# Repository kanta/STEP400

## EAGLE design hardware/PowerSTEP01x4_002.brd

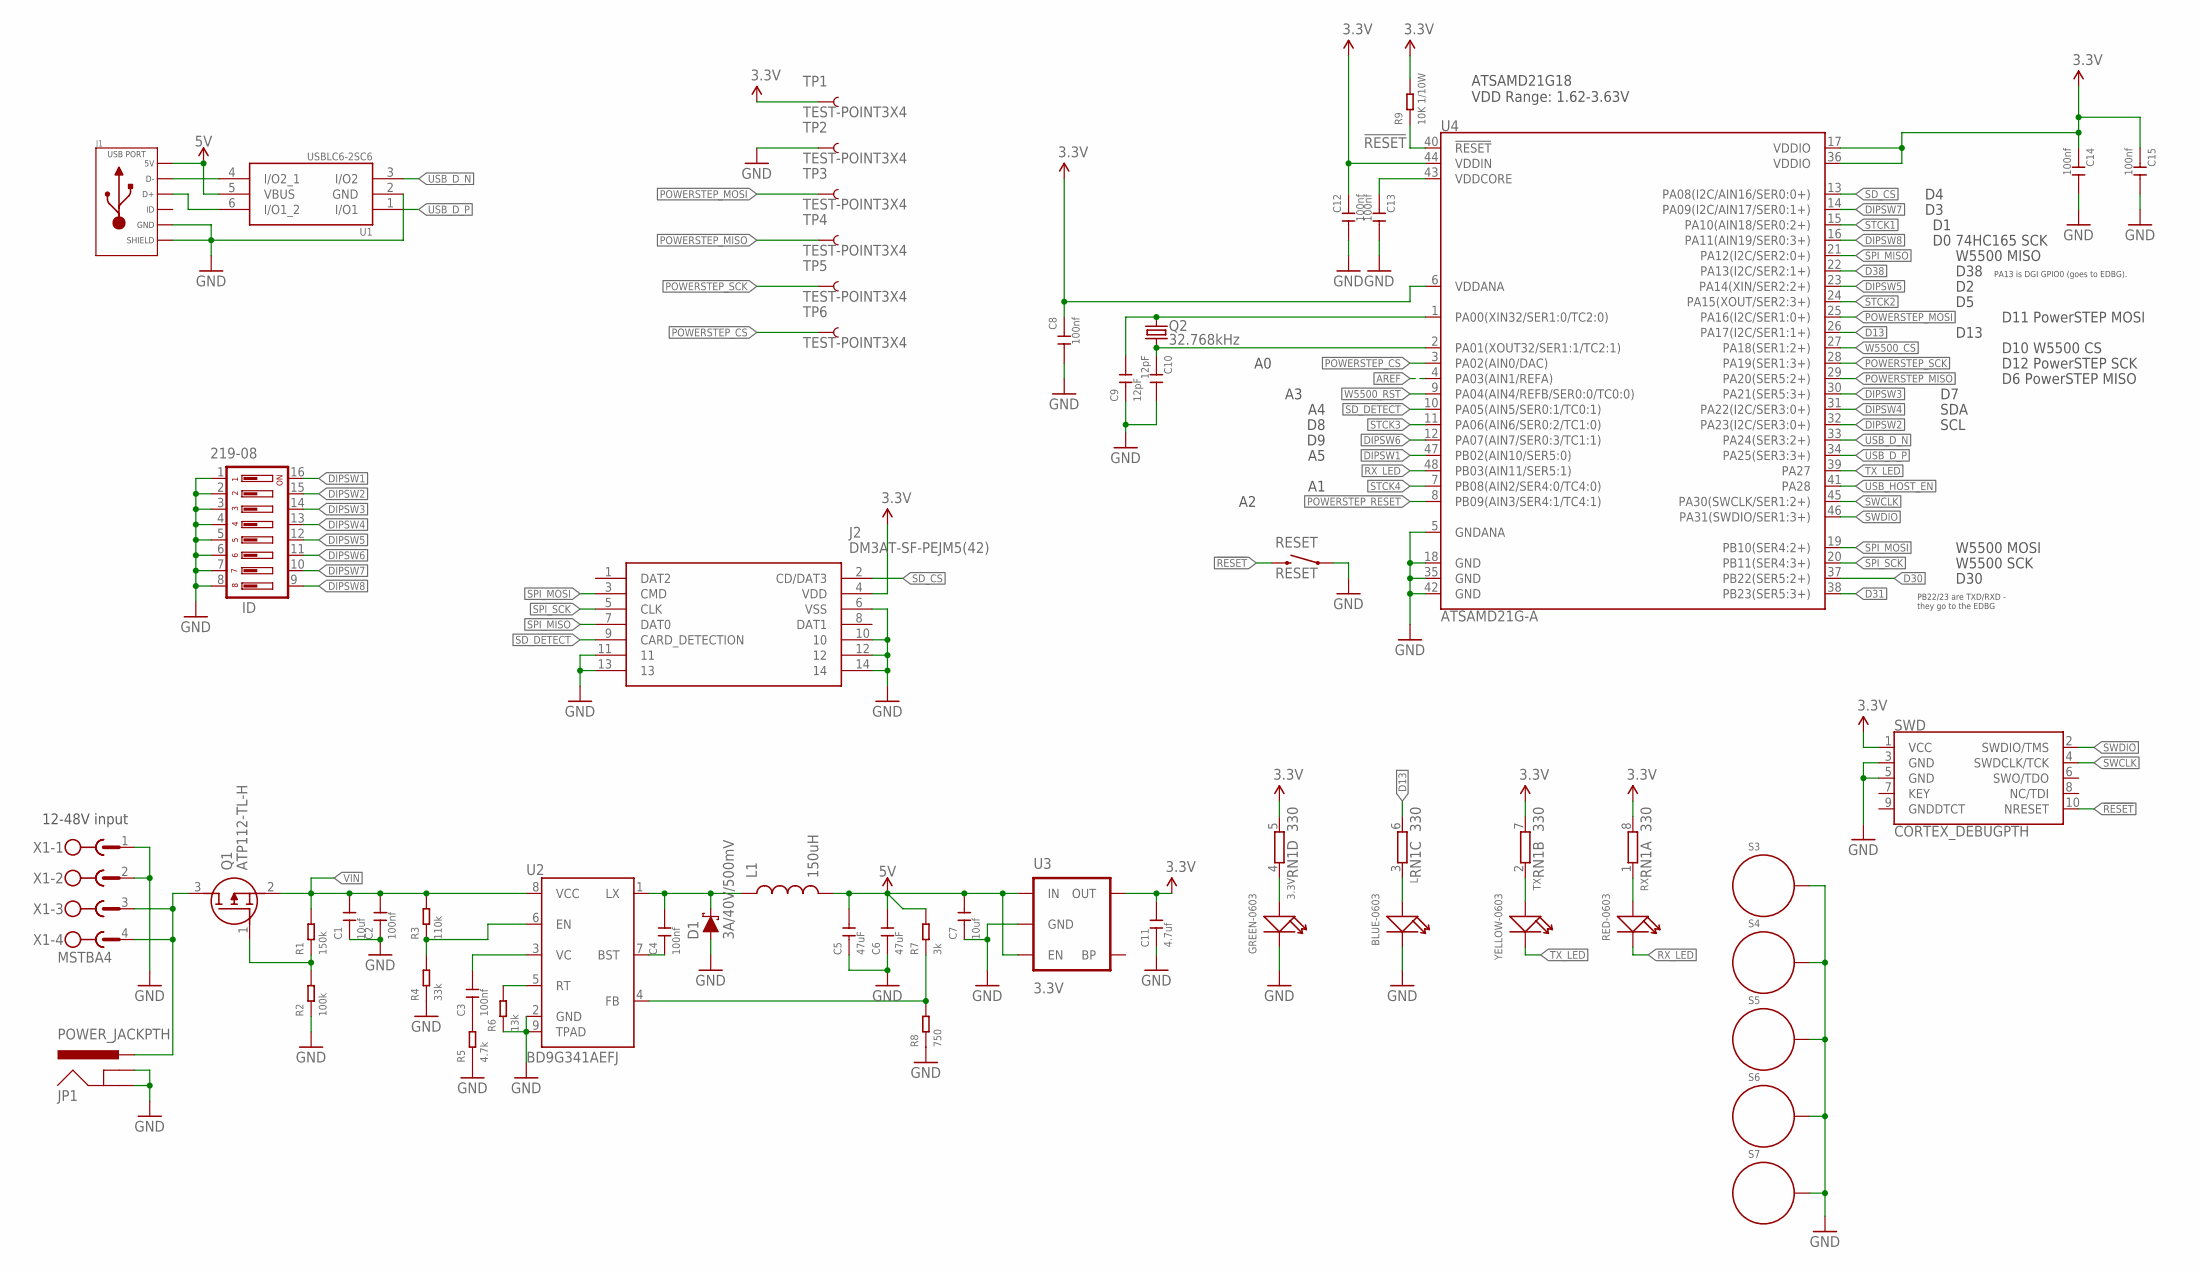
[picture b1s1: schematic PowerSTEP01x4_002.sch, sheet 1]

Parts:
3.3V: GREEN-0603; LED-0603
C1: 10uf; C1206
C2, C3, C4: 100nf; C0603
C5, C6: 47uF; C1206
C7: 10uf; C0805
C8, C12, C13, C14, C15: 100nf; C0402
C9, C10: 12pF; C0402
C11: 4.7uf; C0603
D1: 3A/40V/500mV; SMA-DIODE
ID: 219-08; CTS-219-08
J1: USB_MICRO_10118193-0001LF; MICROUSB-FCI-PBAN
J2: DM3AT-SF-PEJM5(42); DM3ATSFPEJM542
JP1: POWER_JACKPTH; POWER_JACK_PTH
L: BLUE-0603; LED-0603
L1: 150uH; L5045_L
Q1: ATP112-TL-H; ATP112TLH
Q2: 32.768kHz; FC-135
R1: 150k; R0603
R2: 100k; R0603
R3: 110k; R0603
R4: 33k; R0603
R5: 4.7k; R0603
R6: 13k; R0603
R7: 3k; R0603
R8: 750; R0603
R9: 10K 1/10W; R0603
RESET: RESET; TACTILE-SWITCH-SMD
RN1: 330; CAY16_LONG_W
RX: RED-0603; LED-0603
S3, S4, S5, S6, S7: STANDOFF_ELECTRICAL; STANDOFF-ELECTRICAL
SWD: CORTEX_DEBUGPTH; 2X5-PTH-1.27MM
TP1, TP2, TP3, TP4, TP5, TP6: TEST-POINT3X4; PAD.03X.04
TX: YELLOW-0603; LED-0603
U1: USBLC6-2SC6; SOT23-6L
U2: BD9G341AEFJ; SOIC127P600X100-9N
U3: 3.3V; SOT23-5
U4: ATSAMD21G-A; TQFP-48
X1: MSTBA4

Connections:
3.3V: C8.1, C11.2, C12.1, C14.1, C15.1, J2.4 (VDD), R9.2, RN1.5 (2), RN1.7 (2), RN1.8 (2), SWD.1 (VCC), TP1.P$1, U3.5 (OUT), U4.6 (VDDANA), U4.17 (VDDIO), U4.36 (VDDIO), U4.44 (VDDIN); also elsewhere on the board
5V: C5.2, C6.2, C7.2, J1.1 (5V), L1.P$2 (2), R7.2, U1.5 (VBUS), U3.1 (IN), U3.3 (EN); also elsewhere on the board
!RESET: R9.1, RESET.3 (2), SWD.10 (NRESET), U4.40 (!RESET!)
AREF: U4.4 (PA03(AIN1/REFA))
D13: RN1.6 (2), U4.26 (PA17(I2C/SER1:1+))
D30: U4.37 (PB22(SER5:2+))
D31: U4.38 (PB23(SER5:3+))
D38: U4.22 (PA13(I2C/SER2:1+))
D+: J1.3 (D+), U1.6 (I/O1_2)
DIPSW1: ID.16, U4.47 (PB02(AIN10/SER5:0))
DIPSW2: ID.15, U4.32 (PA23(I2C/SER3:0+))
DIPSW3: ID.14, U4.30 (PA21(SER5:3+))
DIPSW4: ID.13, U4.31 (PA22(I2C/SER3:0+))
DIPSW5: ID.12, U4.23 (PA14(XIN/SER2:2+))
DIPSW6: ID.11, U4.12 (PA07(AIN7/SER0:3/TC1:1))
DIPSW7: ID.10, U4.14 (PA09(I2C/AIN17/SER0:1+))
DIPSW8: ID.9, U4.16 (PA11(AIN19/SER0:3+))
GND: 3.3V.-, C1.1, C2.1, C5.1, C6.1, C7.1, C8.2, C9.1, C10.2, C11.1, C12.2, C13.2, C14.2, C15.2, D1.A, ID.1, ID.2, ID.3, ID.4, ID.5, ID.6, ID.7, ID.8, J1.5 (GND), J1.S1 (SLD), J1.S2 (SLD), J1.S3 (SLD), J1.S4 (SLD), J1.S5 (SLD), J1.S6 (SLD), J1.S7 (SLD), J1.S8 (SLD), J2.6 (VSS), J2.10, J2.11, J2.12, J2.13, J2.14, JP1.GND, JP1.GNDBREAK, L.-, R2.1, R4.1, R5.1, R6.1, R8.1, RESET.1, S3.P1, S4.P1, S5.P1, S6.P1, S7.P1, SWD.3 (GND), SWD.5 (GND), TP2.P$1, U1.2 (GND), U2.2 (GND), U2.9 (TPAD), U3.2 (GND), U4.5 (GNDANA), U4.18 (GND), U4.35 (GND), U4.42 (GND), X1.1, X1.2; also elsewhere on the board
unnamed: C9.2, Q2.P$2 (2), U4.1 (PA00(XIN32/SER1:0/TC2:0))
unnamed: C3.1, R5.2
unnamed: C10.1, Q2.P$1 (1), U4.2 (PA01(XOUT32/SER1:1/TC2:1))
unnamed: RN1.1, RX.+
unnamed: RN1.2 (1), TX.+
unnamed: R7.1, R8.2, U2.4 (FB)
unnamed: R3.1, R4.2, U2.6 (EN)
unnamed: R6.2, U2.5 (RT)
unnamed: L.+, RN1.3 (1)
unnamed: 3.3V.+, RN1.4 (1)
unnamed: C3.2, U2.3 (VC)
unnamed: C4.1, U2.7 (BST)
unnamed: C4.2, D1.C, L1.P$1 (1), U2.1 (LX)
unnamed: Q1.1 (G), R1.1, R2.2
unnamed: J1.2 (D-), U1.4 (I/O2_1)
POWERSTEP_CS: TP6.P$1, U4.3 (PA02(AIN0/DAC)); also elsewhere on the board
POWERSTEP_MISO: TP4.P$1, U4.29 (PA20(SER5:2+)); also elsewhere on the board
POWERSTEP_MOSI: TP3.P$1, U4.25 (PA16(I2C/SER1:0+)); also elsewhere on the board
POWERSTEP_RESET: U4.8 (PB09(AIN3/SER4:1/TC4:1)); also elsewhere on the board
POWERSTEP_SCK: TP5.P$1, U4.28 (PA19(SER1:3+)); also elsewhere on the board
RX_LED: RX.-, U4.48 (PB03(AIN11/SER5:1))
SD_CS: J2.2 (CD/DAT3), U4.13 (PA08(I2C/AIN16/SER0:0+))
SD_DETECT: J2.9 (CARD_DETECTION), U4.10 (PA05(AIN5/SER0:1/TC0:1))
SPI_MISO: J2.7 (DAT0), U4.21 (PA12(I2C/SER2:0+)); also elsewhere on the board
SPI_MOSI: J2.3 (CMD), U4.19 (PB10(SER4:2+)); also elsewhere on the board
SPI_SCK: J2.5 (CLK), U4.20 (PB11(SER4:3+)); also elsewhere on the board
STCK1: U4.15 (PA10(AIN18/SER0:2+)); also elsewhere on the board
STCK2: U4.24 (PA15(XOUT/SER2:3+)); also elsewhere on the board
STCK3: U4.11 (PA06(AIN6/SER0:2/TC1:0)); also elsewhere on the board
STCK4: U4.7 (PB08(AIN2/SER4:0/TC4:0)); also elsewhere on the board
SWCLK: SWD.4 (SWDCLK/TCK), U4.45 (PA30(SWCLK/SER1:2+))
SWDIO: SWD.2 (SWDIO/TMS), U4.46 (PA31(SWDIO/SER1:3+))
TX_LED: TX.-, U4.39 (PA27)
USB_D_N: U1.3 (I/O2), U4.33 (PA24(SER3:2+))
USB_D_P: U1.1 (I/O1), U4.34 (PA25(SER3:3+))
USB_HOST_EN: U4.41 (PA28)
VDDCORE: C13.1, U4.43 (VDDCORE)
VIN: C1.2, C2.2, Q1.2 (S), R1.2, R3.2, U2.8 (VCC); also elsewhere on the board
VRAW: JP1.PWR, Q1.3 (D), X1.3, X1.4
W5500_CS: U4.27 (PA18(SER1:2+)); also elsewhere on the board
W5500_RST: U4.9 (PA04(AIN4/REFB/SER0:0/TC0:0)); also elsewhere on the board

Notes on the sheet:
PB22/23 are TXD/RXD - they go to the EDBG
PA13 is DGI GPIO0 (goes to EDBG).
ATSAMD21G18 VDD Range: 1.62-3.63V
D30
D12 PowerSTEP SCK
D10 W5500 CS
D11 PowerSTEP MOSI
D13
D6 PowerSTEP MISO
D38
D0 74HC165 SCK
12-48V input
W5500 MISO
W5500 MOSI
W5500 SCK
SDA
SCL

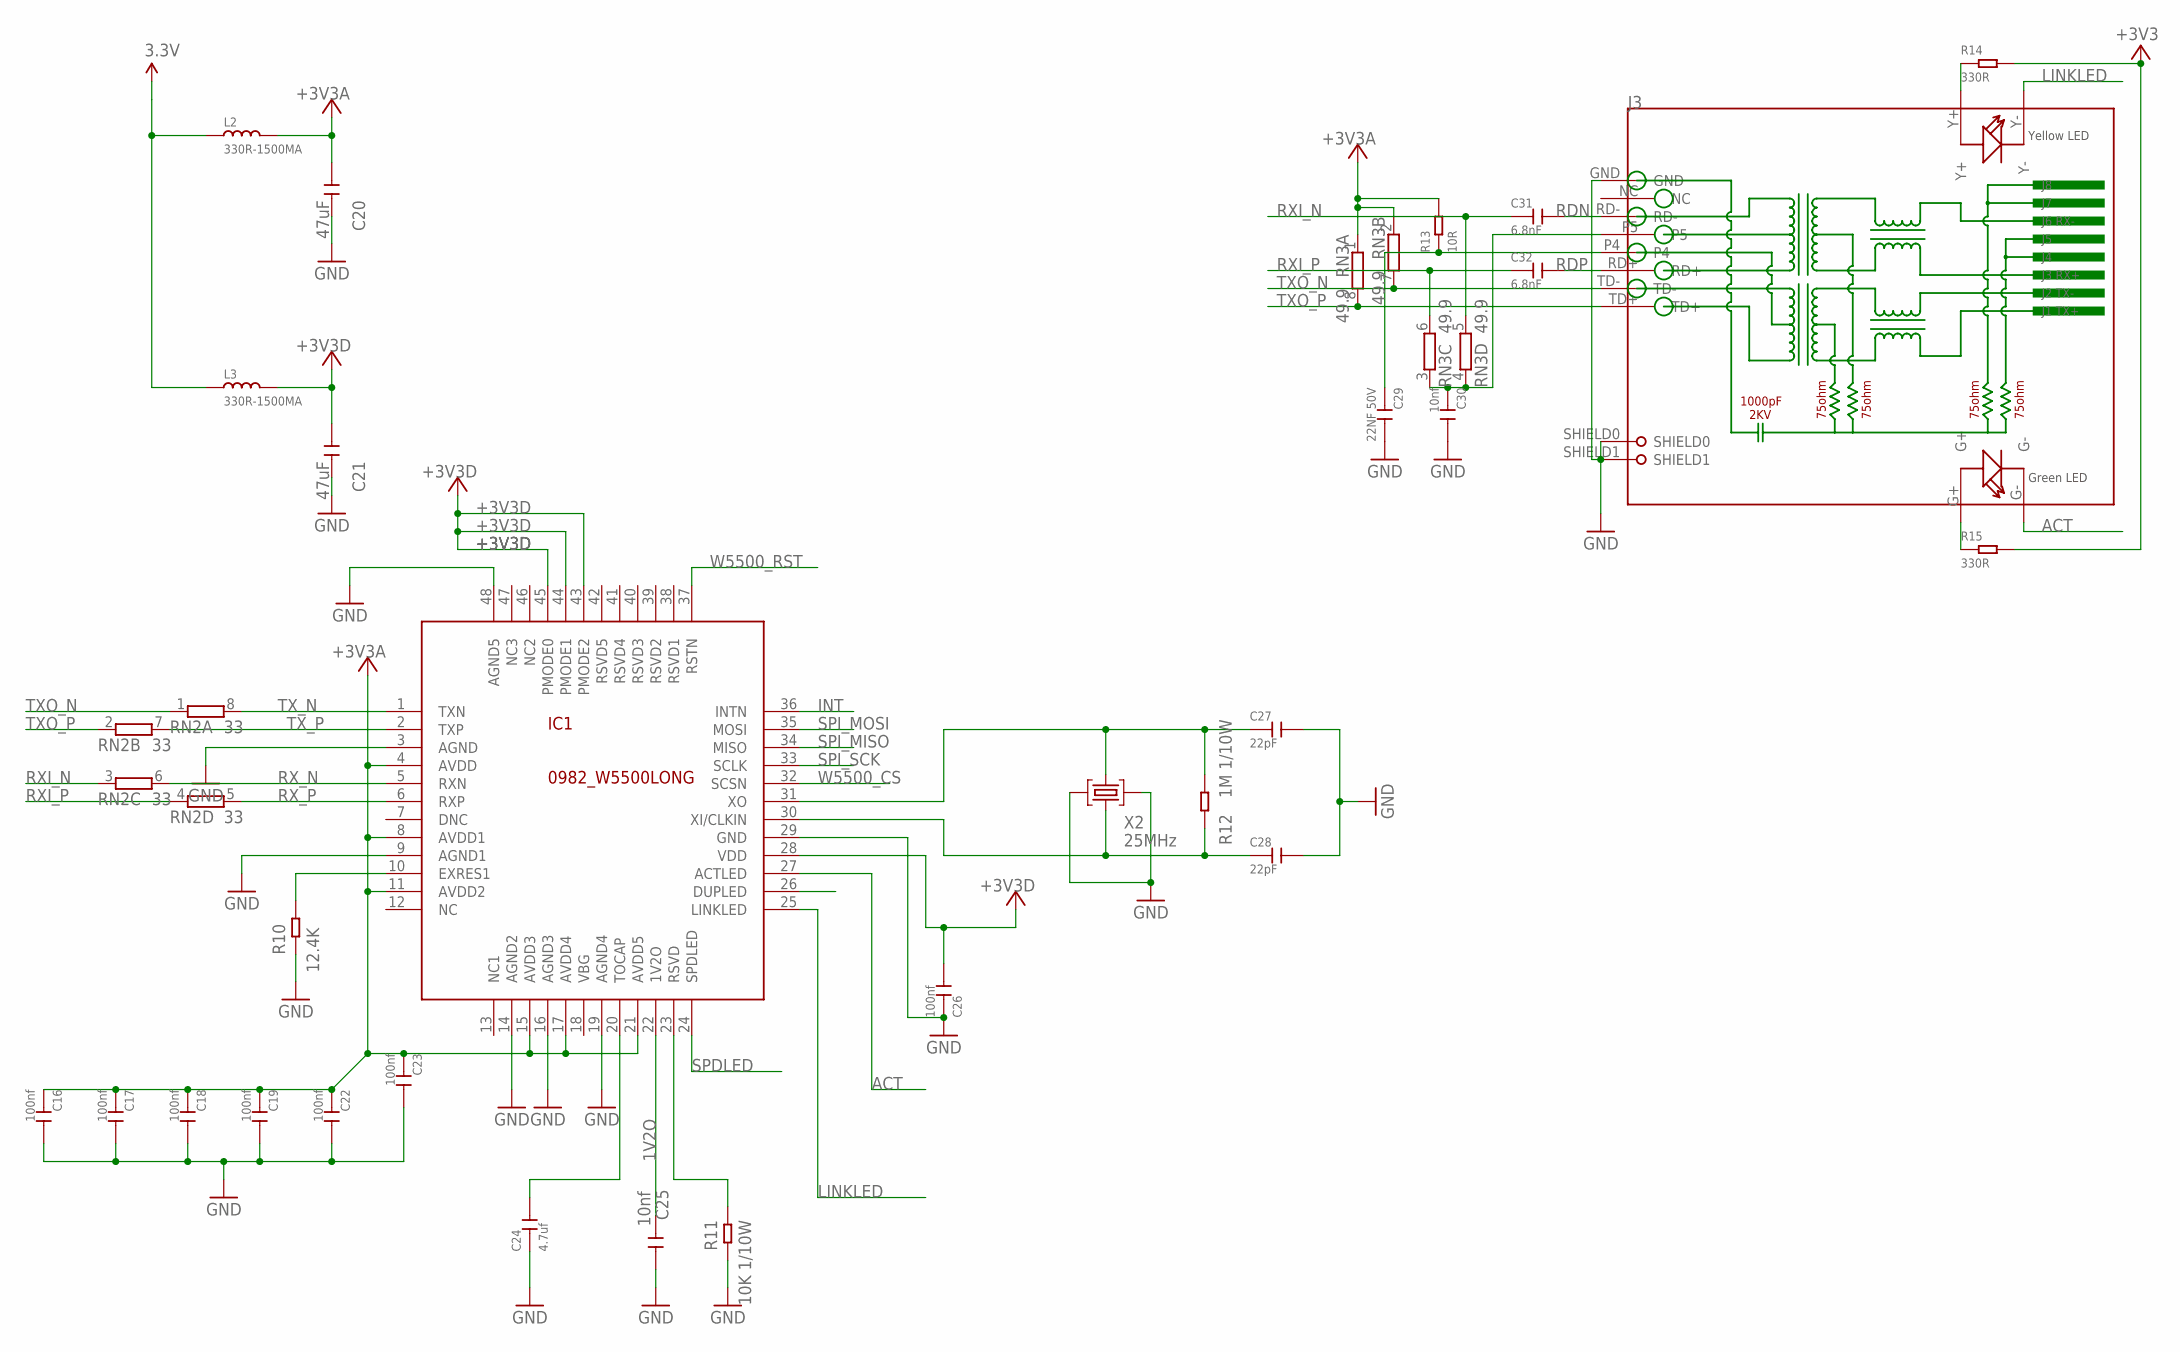
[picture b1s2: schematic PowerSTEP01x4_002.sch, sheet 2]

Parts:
C16, C17, C18, C19, C22, C23, C26: 100nf; C0402
C20, C21: 47uF; C1206
C24: 4.7uf; C0603
C25, C30: 10nf; C0402
C27, C28: 22pF; C0402
C29: 22NF 50V; C0402
C31, C32: 6.8nF; C0402
IC1: 0982_W5500LONG; TQFP48-LONG
J3: RJ45-HR911105A-HR911105A; RJ45
L2, L3: 330R-1500MA; L0805
R10: 12.4K; R0603
R11: 10K 1/10W; R0603
R12: 1M 1/10W; R0603
R13: 10R; R0603
R14, R15: 330R; R0603
RN2: 33; CAY16_LONG_W
RN3: 49.9; CAY16_LONG_W
X2: 25MHz; CRYSTAL-3.2-2.5

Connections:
1V2O: C25.2, IC1.22 (1V2O)
3.3V: L2.1, L3.1, R14.2, R15.2; also elsewhere on the board
+3V3A: C16.1, C17.1, C18.1, C19.1, C20.1, C22.1, C23.1, IC1.4 (AVDD), IC1.8 (AVDD1), IC1.11 (AVDD2), IC1.15 (AVDD3), IC1.17 (AVDD4), IC1.21 (AVDD5), L2.2, R13.2, RN3.1, RN3.2 (1)
+3V3D: C21.1, C26.2, IC1.28 (VDD), IC1.43 (PMODE2), IC1.44 (PMODE1), IC1.45 (PMODE0), L3.2
ACT: IC1.27 (ACTLED), J3.G-
FDXLED: IC1.26 (DUPLED)
GND: C16.2, C17.2, C18.2, C19.2, C20.2, C21.2, C22.2, C23.2, C24.1, C25.1, C26.1, C27.2, C28.2, C29.2, C30.2, IC1.3 (AGND), IC1.9 (AGND1), IC1.14 (AGND2), IC1.16 (AGND3), IC1.19 (AGND4), IC1.29 (GND), IC1.48 (AGND5), J3.GND, J3.SHIELD0, J3.SHIELD1, R10.1, R11.1, X2.2 (GND), X2.4 (GND); also elsewhere on the board
INT: IC1.36 (INTN)
LINKLED: IC1.25 (LINKLED), J3.Y-
unnamed: C27.1, IC1.31 (XO), R12.1, X2.3 (C2)
unnamed: C29.1, J3.P4, R13.1
unnamed: C30.1, J3.P5, RN3.3 (1), RN3.4 (1)
unnamed: J3.Y+, R14.1
unnamed: J3.G+, R15.1
unnamed: IC1.23 (RSVD), R11.2
unnamed: C24.2, IC1.20 (TOCAP)
unnamed: IC1.10 (EXRES1), R10.2
NC: IC1.12 (NC)
OSC2E2: C28.1, IC1.30 (XI/CLKIN), R12.2, X2.1 (C1)
RDN: C31.2, J3.RD-
RDP: C32.2, J3.RD+
RSVD1: IC1.38 (RSVD1)
RSVD2: IC1.39 (RSVD2)
RSVD3: IC1.40 (RSVD3)
RXI_N: C31.1, RN2.3 (1), RN3.5 (2)
RXI_P: C32.1, RN2.4 (1), RN3.6 (2)
RX_N: IC1.5 (RXN), RN2.6 (2)
RX_P: IC1.6 (RXP), RN2.5 (2)
SPDLED: IC1.24 (SPDLED)
SPI_MISO: IC1.34 (MISO); also elsewhere on the board
SPI_MOSI: IC1.35 (MOSI); also elsewhere on the board
SPI_SCK: IC1.33 (SCLK); also elsewhere on the board
TXO_N: J3.TD-, RN2.1, RN3.7 (2)
TXO_P: J3.TD+, RN2.2 (1), RN3.8 (2)
TX_N: IC1.1 (TXN), RN2.8 (2)
TX_P: IC1.2 (TXP), RN2.7 (2)
W5500_CS: IC1.32 (SCSN); also elsewhere on the board
W5500_RST: IC1.37 (RSTN); also elsewhere on the board

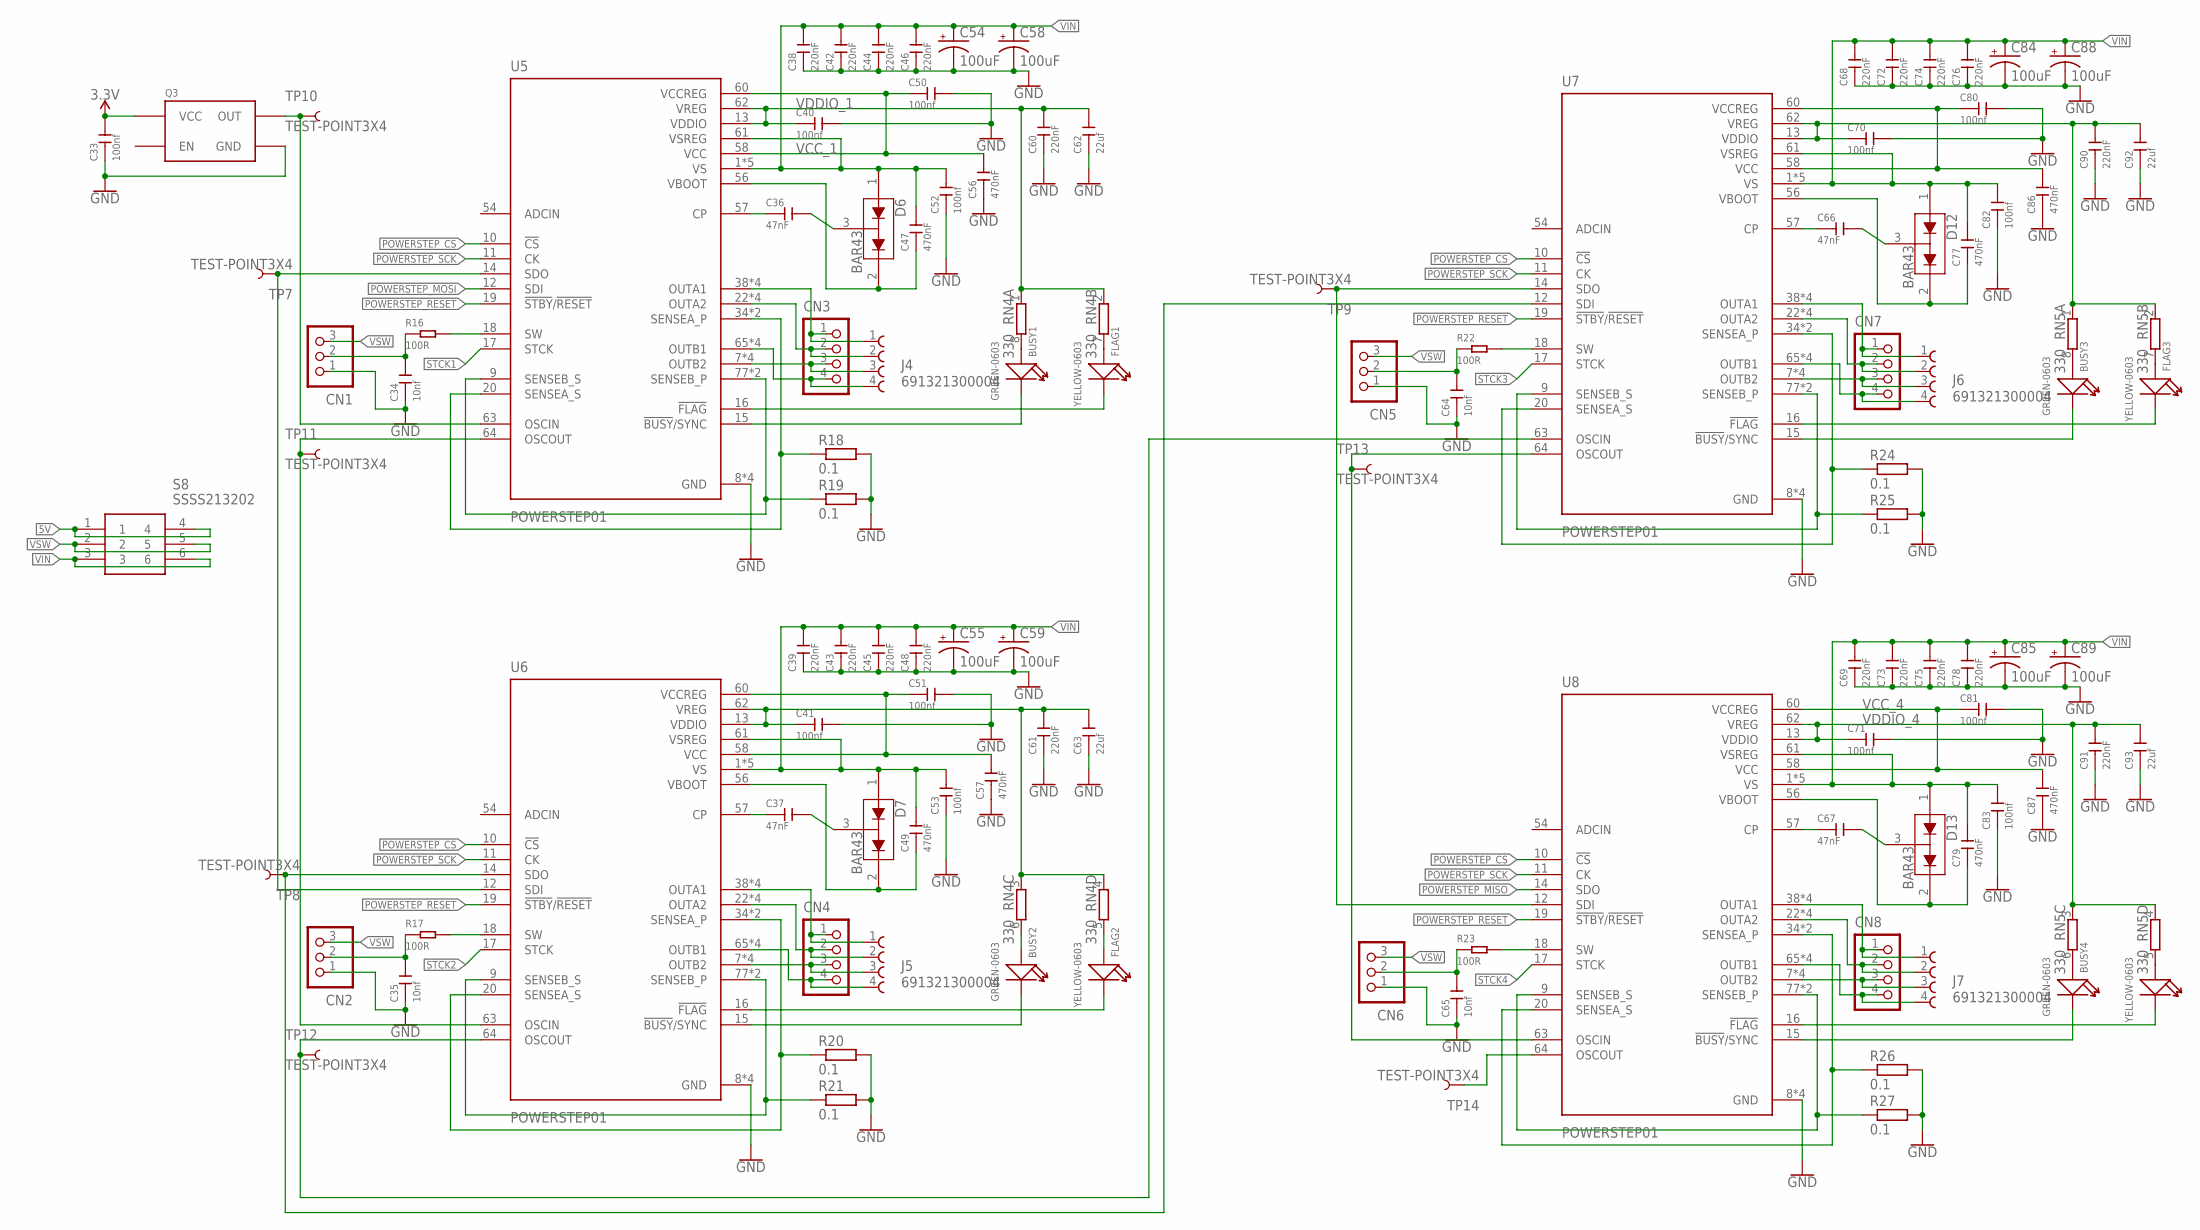
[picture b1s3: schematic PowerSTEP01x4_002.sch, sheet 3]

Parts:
BUSY1, BUSY2, BUSY3, BUSY4: GREEN-0603; LED-0603
C33, C40, C41, C50, C51, C70, C71, C80, C81: 100nf; C0402
C34, C35, C64, C65: 10nf; C0402
C36, C37, C66, C67: 47nF; C0603
C38, C39, C42, C43, C44, C45, C46, C48, C68, C69, C72, C73, C74, C75, C76, C78: 220nF; C0805
C47, C49, C56, C57, C77, C79, C86, C87: 470nF; C0603
C52, C53, C82, C83: 100nf; C0603
C54, C55, C58, C59, C84, C85, C88, C89: 100uF; C_POL_D8
C60, C61, C90, C91: 220nF; C0402
C62, C63, C92, C93: 22uf; C0805
CN1, CN2, CN5, CN6: B3B-XASK-1
CN3, CN4, CN7, CN8: B4B-XASK-1
D6, D7, D12, D13: BAR43; SOT23-3
FLAG1, FLAG2, FLAG3, FLAG4: YELLOW-0603; LED-0603
J4, J5, J6, J7: 691321300004
Q3: CRYSTAL_OSC_SG5032; SG5032
R16, R17, R22, R23: 100R; R0603
R18, R19, R20, R21, R24, R25, R26, R27: 0.1; RESC6332X71N
RN4, RN5: 330; CAY16_LONG_W
S8: SSSS213202
TP7, TP8, TP9, TP10, TP11, TP12, TP13, TP14: TEST-POINT3X4; PAD.03X.04
U5, U6, U7, U8: POWERSTEP01; IC_POWERSTEP01

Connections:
3.3V: C33.2, Q3.4 (VCC); also elsewhere on the board
5V: S8.1, S8.4; also elsewhere on the board
GND: C33.1, C34.1, C35.1, C38.1, C39.1, C40.2, C41.2, C42.1, C43.1, C44.1, C45.1, C46.1, C48.1, C50.2, C51.2, C52.1, C53.1, C54.-, C55.-, C56.1, C57.1, C58.-, C59.-, C60.1, C61.1, C62.1, C63.1, C64.1, C65.1, C68.1, C69.1, C70.2, C71.2, C72.1, C73.1, C74.1, C75.1, C76.1, C78.1, C80.2, C81.2, C82.1, C83.1, C84.-, C85.-, C86.1, C87.1, C88.-, C89.-, C90.1, C91.1, C92.1, C93.1, CN1.1, CN2.1, CN5.1, CN6.1, Q3.2 (GND), R18.2, R19.2, R20.2, R21.2, R24.2, R25.2, R26.2, R27.2, U5.8 (GND), U5.21 (GND), U5.59 (GND), U5.EPAD9 (GND), U6.8 (GND), U6.21 (GND), U6.59 (GND), U6.EPAD9 (GND), U7.8 (GND), U7.21 (GND), U7.59 (GND), U7.EPAD9 (GND), U8.8 (GND), U8.21 (GND), U8.59 (GND), U8.EPAD9 (GND); also elsewhere on the board
unnamed: TP14.P$1, U8.64 (OSCOUT)
unnamed: BUSY1.+, RN4.8 (2)
unnamed: FLAG1.+, RN4.7 (2)
unnamed: C36.2, D6.3 (COM)
unnamed: C36.1, U5.57 (CP)
unnamed: BUSY2.+, RN4.6 (2)
unnamed: FLAG2.+, RN4.5 (2)
unnamed: FLAG1.-, U5.16 (!FLAG)
unnamed: BUSY1.-, U5.15 (!BUSY!/SYNC)
unnamed: R19.1, U5.9 (SENSEB_S), U5.77 (SENSEB_P), U5.82 (SENSEB_P)
unnamed: R18.1, U5.20 (SENSEA_S), U5.34 (SENSEA_P), U5.39 (SENSEA_P)
unnamed: R16.2, U5.18 (SW)
unnamed: C34.2, CN1.2, R16.1
unnamed: CN3.1, J4.1, U5.38 (OUTA1), U5.42 (OUTA1), U5.53 (OUTA1), U5.EPAD4 (OUTA1)
unnamed: CN3.2, J4.2, U5.22 (OUTA2), U5.33 (OUTA2), U5.37 (OUTA2), U5.EPAD3 (OUTA2)
unnamed: TP7.P$1, U5.14 (SDO), U6.12 (SDI)
unnamed: CN3.3, J4.3, U5.7 (OUTB2), U5.81 (OUTB2), U5.85 (OUTB2), U5.EPAD8 (OUTB2)
unnamed: CN3.4, J4.4, U5.65 (OUTB1), U5.76 (OUTB1), U5.80 (OUTB1), U5.EPAD7 (OUTB1)
unnamed: C37.2, D7.3 (COM)
unnamed: C37.1, U6.57 (CP)
unnamed: BUSY3.+, RN5.8 (2)
unnamed: FLAG3.+, RN5.7 (2)
unnamed: FLAG2.-, U6.16 (!FLAG)
unnamed: BUSY2.-, U6.15 (!BUSY!/SYNC)
unnamed: R21.1, U6.9 (SENSEB_S), U6.77 (SENSEB_P), U6.82 (SENSEB_P)
unnamed: R20.1, U6.20 (SENSEA_S), U6.34 (SENSEA_P), U6.39 (SENSEA_P)
unnamed: R17.2, U6.18 (SW)
unnamed: TP12.P$1, U6.64 (OSCOUT), U7.63 (OSCIN)
unnamed: CN4.1, J5.1, U6.38 (OUTA1), U6.42 (OUTA1), U6.53 (OUTA1), U6.EPAD4 (OUTA1)
unnamed: CN4.2, J5.2, U6.22 (OUTA2), U6.33 (OUTA2), U6.37 (OUTA2), U6.EPAD3 (OUTA2)
unnamed: CN4.3, J5.3, U6.7 (OUTB2), U6.81 (OUTB2), U6.85 (OUTB2), U6.EPAD8 (OUTB2)
unnamed: CN4.4, J5.4, U6.65 (OUTB1), U6.76 (OUTB1), U6.80 (OUTB1), U6.EPAD7 (OUTB1)
unnamed: C35.2, CN2.2, R17.1
unnamed: BUSY4.+, RN5.6 (2)
unnamed: C77.1, D12.2 (C2), U7.56 (VBOOT)
unnamed: C66.2, D12.3 (COM)
unnamed: C66.1, U7.57 (CP)
unnamed: FLAG4.+, RN5.5 (2)
unnamed: CN7.4, J6.4, U7.65 (OUTB1), U7.76 (OUTB1), U7.80 (OUTB1), U7.EPAD7 (OUTB1)
unnamed: FLAG3.-, U7.16 (!FLAG)
unnamed: BUSY3.-, U7.15 (!BUSY!/SYNC)
unnamed: R25.1, U7.9 (SENSEB_S), U7.77 (SENSEB_P), U7.82 (SENSEB_P)
unnamed: R24.1, U7.20 (SENSEA_S), U7.34 (SENSEA_P), U7.39 (SENSEA_P)
unnamed: R22.2, U7.18 (SW)
unnamed: TP8.P$1, U6.14 (SDO), U7.12 (SDI)
unnamed: CN7.1, J6.1, U7.38 (OUTA1), U7.42 (OUTA1), U7.53 (OUTA1), U7.EPAD4 (OUTA1)
unnamed: CN7.2, J6.2, U7.22 (OUTA2), U7.33 (OUTA2), U7.37 (OUTA2), U7.EPAD3 (OUTA2)
unnamed: CN7.3, J6.3, U7.7 (OUTB2), U7.81 (OUTB2), U7.85 (OUTB2), U7.EPAD8 (OUTB2)
unnamed: CN8.4, J7.4, U8.65 (OUTB1), U8.76 (OUTB1), U8.80 (OUTB1), U8.EPAD7 (OUTB1)
unnamed: C64.2, CN5.2, R22.1
unnamed: CN8.3, J7.3, U8.7 (OUTB2), U8.81 (OUTB2), U8.85 (OUTB2), U8.EPAD8 (OUTB2)
unnamed: C79.1, D13.2 (C2), U8.56 (VBOOT)
unnamed: C67.2, D13.3 (COM)
unnamed: C67.1, U8.57 (CP)
unnamed: FLAG4.-, U8.16 (!FLAG)
unnamed: BUSY4.-, U8.15 (!BUSY!/SYNC)
unnamed: R27.1, U8.9 (SENSEB_S), U8.77 (SENSEB_P), U8.82 (SENSEB_P)
unnamed: R26.1, U8.20 (SENSEA_S), U8.34 (SENSEA_P), U8.39 (SENSEA_P)
unnamed: R23.2, U8.18 (SW)
unnamed: CN8.1, J7.1, U8.38 (OUTA1), U8.42 (OUTA1), U8.53 (OUTA1), U8.EPAD4 (OUTA1)
unnamed: CN8.2, J7.2, U8.22 (OUTA2), U8.33 (OUTA2), U8.37 (OUTA2), U8.EPAD3 (OUTA2)
unnamed: C65.2, CN6.2, R23.1
unnamed: Q3.3 (OUT), TP10.P$1, U5.63 (OSCIN)
unnamed: TP11.P$1, U5.64 (OSCOUT), U6.63 (OSCIN)
unnamed: TP13.P$1, U7.64 (OSCOUT), U8.63 (OSCIN)
unnamed: TP9.P$1, U7.14 (SDO), U8.12 (SDI)
POWERSTEP_CS: U5.10 (!CS), U6.10 (!CS), U7.10 (!CS), U8.10 (!CS); also elsewhere on the board
POWERSTEP_MISO: U8.14 (SDO); also elsewhere on the board
POWERSTEP_MOSI: U5.12 (SDI); also elsewhere on the board
POWERSTEP_RESET: U5.19 (!STBY!/!RESET), U6.19 (!STBY!/!RESET), U7.19 (!STBY!/!RESET), U8.19 (!STBY!/!RESET); also elsewhere on the board
POWERSTEP_SCK: U5.11 (CK), U6.11 (CK), U7.11 (CK), U8.11 (CK); also elsewhere on the board
STCK1: U5.17 (STCK); also elsewhere on the board
STCK2: U6.17 (STCK); also elsewhere on the board
STCK3: U7.17 (STCK); also elsewhere on the board
STCK4: U8.17 (STCK); also elsewhere on the board
VBOOT_1: C47.1, D6.2 (C2), U5.56 (VBOOT)
VBOOT_2: C49.1, D7.2 (C2), U6.56 (VBOOT)
VCC_1: C50.1, C56.2, U5.58 (VCC), U5.60 (VCCREG)
VCC_2: C51.1, C57.2, U6.58 (VCC), U6.60 (VCCREG)
VCC_3: C80.1, C86.2, U7.58 (VCC), U7.60 (VCCREG)
VCC_4: C81.1, C87.2, U8.58 (VCC), U8.60 (VCCREG)
VDDIO_1: C40.1, C60.2, C62.2, RN4.1, RN4.2 (1), U5.13 (VDDIO), U5.62 (VREG)
VDDIO_2: C41.1, C61.2, C63.2, RN4.3 (1), RN4.4 (1), U6.13 (VDDIO), U6.62 (VREG)
VDDIO_3: C70.1, C90.2, C92.2, RN5.1, RN5.2 (1), U7.13 (VDDIO), U7.62 (VREG)
VDDIO_4: C71.1, C91.2, C93.2, RN5.3 (1), RN5.4 (1), U8.13 (VDDIO), U8.62 (VREG)
VIN: C38.2, C39.2, C42.2, C43.2, C44.2, C45.2, C46.2, C47.2, C48.2, C49.2, C52.2, C53.2, C54.+, C55.+, C58.+, C59.+, C68.2, C69.2, C72.2, C73.2, C74.2, C75.2, C76.2, C77.2, C78.2, C79.2, C82.2, C83.2, C84.+, C85.+, C88.+, C89.+, D6.1 (A1), D7.1 (A1), D12.1 (A1), D13.1 (A1), S8.3, S8.6, U5.1 (VS), U5.23 (VS), U5.43 (VS), U5.55 (VS), U5.61 (VSREG), U5.66 (VS), U6.1 (VS), U6.23 (VS), U6.43 (VS), U6.55 (VS), U6.61 (VSREG), U6.66 (VS), U7.1 (VS), U7.23 (VS), U7.43 (VS), U7.55 (VS), U7.61 (VSREG), U7.66 (VS), U8.1 (VS), U8.23 (VS), U8.43 (VS), U8.55 (VS), U8.61 (VSREG), U8.66 (VS); also elsewhere on the board
VSW: CN1.3, CN2.3, CN5.3, CN6.3, S8.2, S8.5

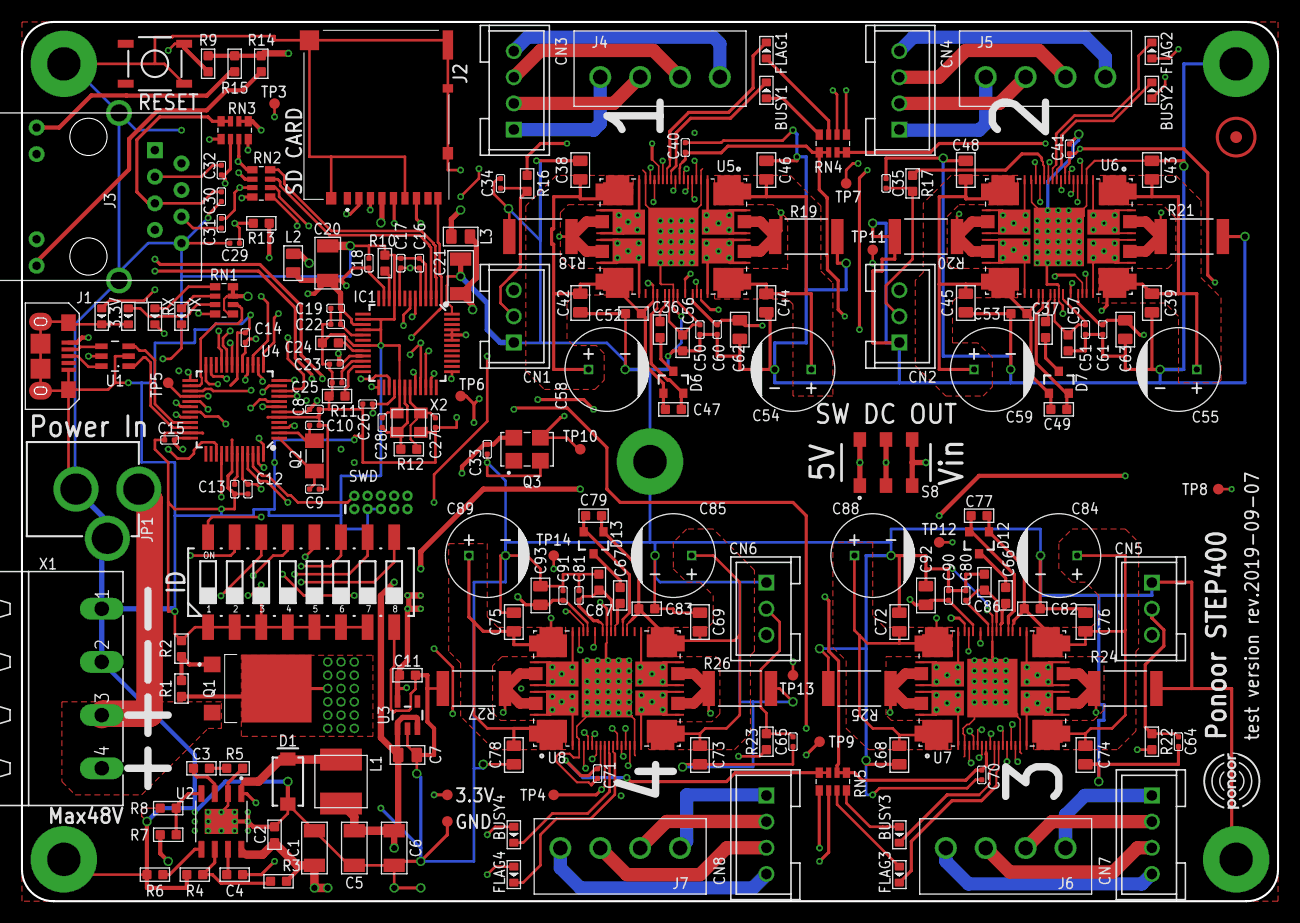
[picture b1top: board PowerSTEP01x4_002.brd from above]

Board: 4 copper layers, 120.0 x 84.0 mm, 200 parts (0 on the bottom side), 155 nets.

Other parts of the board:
U$1: FIDUCIAL_MARKER_PBAN
U$3: PONOOR_LOGO_6MM

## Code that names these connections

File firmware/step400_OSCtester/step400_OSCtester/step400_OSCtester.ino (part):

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
#define W5500_RESET A3

#define POWERSTEP_MISO	6	// D6 /SERCOM3/PAD[2] miso
#define POWERSTEP_MOSI	11	// D11/SERCOM3/PAD[0] mosi
#define POWERSTEP_SCK	12	// D12/SERCOM3/PAD[3] sck
//SPIClass altSPI (&sercom1, 12, 13, 11, SPI_PAD_0_SCK_1, SERCOM_RX_PAD_3);
SPIClass powerStepSPI (&sercom3, POWERSTEP_MISO, POWERSTEP_SCK, POWERSTEP_MOSI, SPI_PAD_0_SCK_3, SERCOM_RX_PAD_2);// MISO/SCK/MOSI pins

#define POWERSTEP_CS_PIN A0
#define POWERSTEP_RESET_PIN A2

#define NUM_POWER_STEP (4)

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// powerSTEP library instance, parameters are distance from the end of a daisy-chain
// of drivers, !CS pin, !STBY/!Reset pin
powerSTEP powerSteps[] = {
	powerSTEP(3, POWERSTEP_CS_PIN, POWERSTEP_RESET_PIN),
	powerSTEP(2, POWERSTEP_CS_PIN, POWERSTEP_RESET_PIN),
	powerSTEP(1, POWERSTEP_CS_PIN, POWERSTEP_RESET_PIN),
	powerSTEP(0, POWERSTEP_CS_PIN, POWERSTEP_RESET_PIN)
};

#define SD_CS	4u

const uint8_t dipSwPin[8] = {A5,SCL,7u,SDA,2u,9u,3u,0u};

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

	pinMode(ledPin, OUTPUT);
	pinMode(SD_CS, OUTPUT);

	// Start serial
	SerialUSB.begin(115200);
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	pinMode(W5500_RESET, OUTPUT);

	// Prepare pins
	pinMode(POWERSTEP_RESET_PIN, OUTPUT);
	pinMode(POWERSTEP_CS_PIN, OUTPUT);
	pinMode(POWERSTEP_MOSI, OUTPUT);
	pinMode(POWERSTEP_MISO, INPUT);
	pinMode(POWERSTEP_SCK, OUTPUT);

	// Reset powerSTEP and set CS
	digitalWrite(POWERSTEP_RESET_PIN, HIGH);
	digitalWrite(POWERSTEP_RESET_PIN, LOW);
	delay(100);
	digitalWrite(POWERSTEP_RESET_PIN, HIGH);
	digitalWrite(POWERSTEP_CS_PIN, HIGH);

	// Start SPI for PowerSTEP
	powerStepSPI.begin();
	// powerStepSPI.setClockDivider(SPI_CLOCK_DIV128); // default 4
	pinPeripheral(POWERSTEP_MOSI, PIO_SERCOM_ALT);
	pinPeripheral(POWERSTEP_SCK, PIO_SERCOM_ALT);
	pinPeripheral(POWERSTEP_MISO , PIO_SERCOM_ALT);
	powerStepSPI.setDataMode(SPI_MODE3);
	delay(100);
	// Configure powerSTEP
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
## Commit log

2019-09-24 initial commit.
2019-10-18 gitignore
2019-10-18 update gitignore
2019-10-18 ライブラリをローカルにしてサブモジュール化
2019-10-18 基本的なコマンドをOSCからたたけるように
2019-10-18 スイッチテスト スラッシュわすれ
2019-10-24 定電流制御のコマンドついか
2019-10-28 gitmodulesをhttpsに
2019-10-28 毎フレームget statusする
2019-10-28 git modkules に branch master ついか
2019-10-29 [nipkow] step400_OSCtester.inoのステータス変更しました。
2019-10-30 [debug] デバッグ用ブランチ作成、Arduino IDEでコンパイルできるようにファイル移動しました。
2019-10-30 [debug] 最後の方が0だったら表示、という風にした
2019-10-31 [debug] とりあえず
2019-10-31 [debug] 多数決/重要な値を拾いたい方式を実装しました。
2019-10-31 [debug] SPIの速さを元に戻しました(4MHz)
2019-11-08 getSw getBusy setSwMode getSwModeついか
2019-11-08 serial.biginしなくてもUSBの接続が問題だった ストリクトにもどす
2019-11-12 svnモーター基板w5500リセット

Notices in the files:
parts and their libraries:
SparkFun-DiscreteSemi: Licensing: Creative Commons ShareAlike 4.0 International - https://creativecommons.org/licenses/by-sa/4.0
SparkFun: Licensing: CC v3.0 Share-Alike You are welcome to use this library for commercial purposes.
